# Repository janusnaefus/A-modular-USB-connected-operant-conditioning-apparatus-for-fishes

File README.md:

# A-modular-USB-connected-operant-conditioning-apparatus-for-fishes
Software and hardware blueprints for the corresponding publication in Behavioral Ecology and Sociobiology

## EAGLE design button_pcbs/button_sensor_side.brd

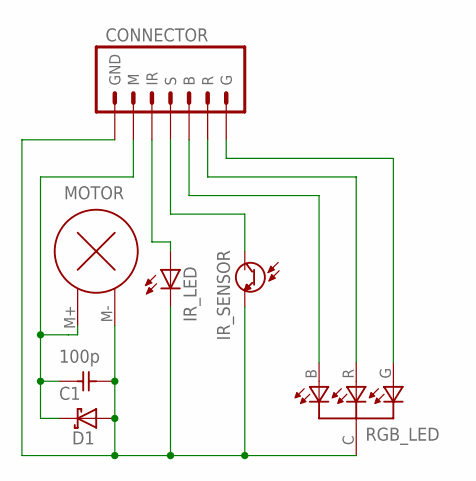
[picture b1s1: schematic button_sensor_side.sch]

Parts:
C1: 100p; C0805
CONNECTOR: CONNECTOR_PADS
D1: DIODE_SCHOTTKY; NSR0530HT1G_SCHOTTKY_DIODE
IR_LED: TCR5000_EMITTER; TCR5000_IR_EMITTER
IR_SENSOR: TCR5000_SENSOR; TCR5000_IR_SENSOR
MOTOR: VIBRATION_MOTOR
RGB_LED: APTF1616SEJ3ZGGVBDC_RBG_LED_SMT; APTF1616SEJ3ZGGVBDC_RGB_LED_SMT

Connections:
GND: C1.2, CONNECTOR.GND, CONNECTOR.GND_ (GND), D1.A, IR_LED.C, IR_SENSOR.E, MOTOR.M- (-), RGB_LED.C
unnamed: C1.1, CONNECTOR.M, D1.C, MOTOR.M+ (+)
unnamed: CONNECTOR.S, IR_SENSOR.C
unnamed: CONNECTOR.IR, IR_LED.A
unnamed: CONNECTOR.B, RGB_LED.B (BLUE)
unnamed: CONNECTOR.R, RGB_LED.R (RED)
unnamed: CONNECTOR.G, RGB_LED.G (GREEN)

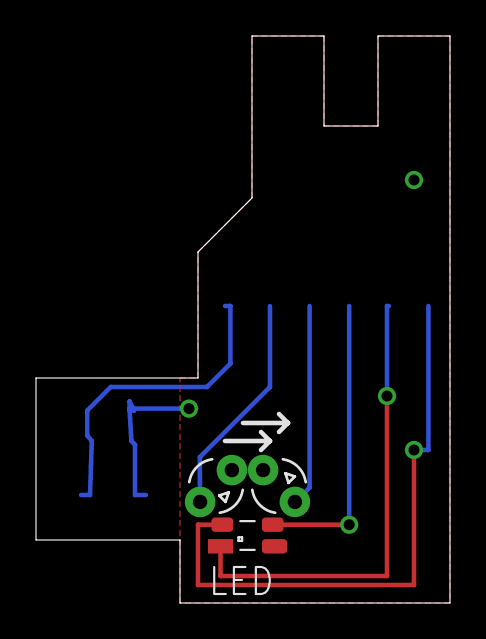
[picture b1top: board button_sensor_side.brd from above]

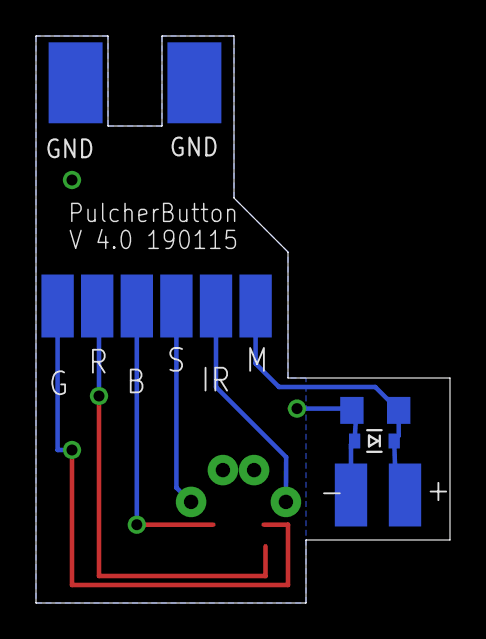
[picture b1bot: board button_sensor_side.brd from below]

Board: 2 copper layers, 23.0 x 31.5 mm, 7 parts (2 on the bottom side), 7 nets.

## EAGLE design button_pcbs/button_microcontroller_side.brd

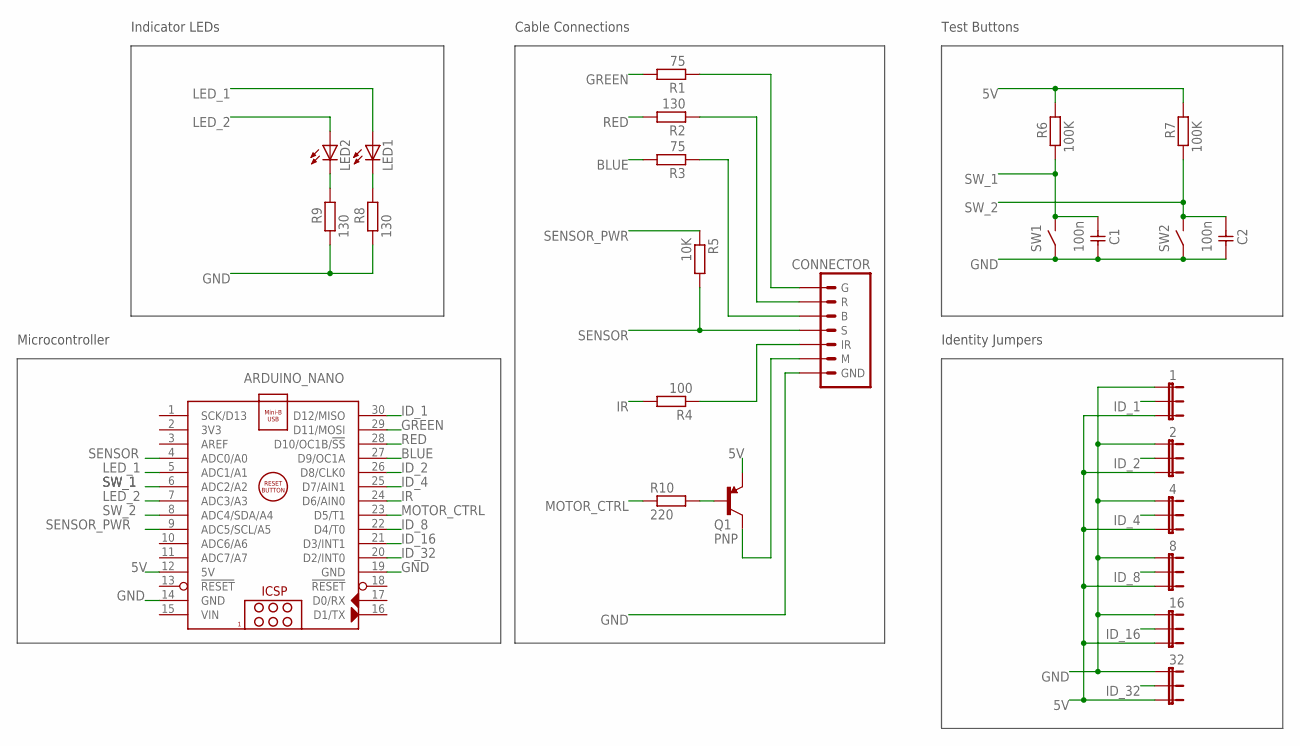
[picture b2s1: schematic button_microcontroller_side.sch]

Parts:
1, 2, 4, 8, 16, 32: JP2E; JP2
ARDUINO_NANO: ARDUINO_NANO
C1, C2: 100n; CAPACITOR
CONNECTOR: CONNECTOR_PADSHOLES; CONNECTOR_ARDUINO_SIDE
LED1, LED2: LED_3MM; TCR5000_IR_EMITTER
Q1: PNP; TO92-
R1, R3: 75; 0204/7
R2, R8, R9: 130; 0204/7
R4: 100; 0204/7
R5: 10K; 0204/7
R6, R7: 100K; 0204/7
R10: 220; 0204/7
SW1, SW2: BUTTON; KS-01Q-01_BUTTON

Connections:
5V: 1.3, 2.3, 4.3, 8.3, 16.3, 32.3, ARDUINO_NANO.12 (5V), Q1.E, R6.2, R7.2
BLUE: ARDUINO_NANO.27 (D9/OC1A), R3.2
GND: 1.1, 2.1, 4.1, 8.1, 16.1, 32.1, ARDUINO_NANO.14 (GND), ARDUINO_NANO.19 (GND), C1.P$1 (1), C2.P$1 (1), CONNECTOR.GND, R8.1, R9.1, SW1.1, SW1.3 (1), SW2.1, SW2.3 (1)
GREEN: ARDUINO_NANO.29 (D11/MOSI), R1.2
ID_1: 1.2, ARDUINO_NANO.30 (D12/MISO)
ID_2: 2.2, ARDUINO_NANO.26 (D8/CLK0)
ID_4: 4.2, ARDUINO_NANO.25 (D7/AIN1)
ID_8: 8.2, ARDUINO_NANO.22 (D4/T0)
ID_16: 16.2, ARDUINO_NANO.21 (D3/INT1)
ID_32: 32.2, ARDUINO_NANO.20 (D2/INT0)
IR: ARDUINO_NANO.24 (D6/AIN0), R4.2
LED_1: ARDUINO_NANO.5 (ADC1/A1), LED1.A
LED_2: ARDUINO_NANO.7 (ADC3/A3), LED2.A
MOTOR: CONNECTOR.M, Q1.C
MOTOR_CTRL: ARDUINO_NANO.23 (D5/T1), R10.1
unnamed: CONNECTOR.IR, R4.1
unnamed: CONNECTOR.B, R3.1
unnamed: CONNECTOR.R, R2.1
unnamed: CONNECTOR.G, R1.1
unnamed: LED1.C, R8.2
unnamed: LED2.C, R9.2
unnamed: Q1.B, R10.2
RED: ARDUINO_NANO.28 (D10/OC1B/!SS), R2.2
SENSOR: ARDUINO_NANO.4 (ADC0/A0), CONNECTOR.S, R5.2
SENSOR_PWR: ARDUINO_NANO.9 (ADC5/SCL/A5), R5.1
SW_1: ARDUINO_NANO.6 (ADC2/A2), C1.P$2 (2), R6.1, SW1.2, SW1.4 (2)
SW_2: ARDUINO_NANO.8 (ADC4/SDA/A4), C2.P$2 (2), R7.1, SW2.2, SW2.4 (2)
VIN: ARDUINO_NANO.15 (VIN)

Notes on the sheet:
Indicator LEDs
Test Buttons
Cable Connections
Identity Jumpers
Microcontroller

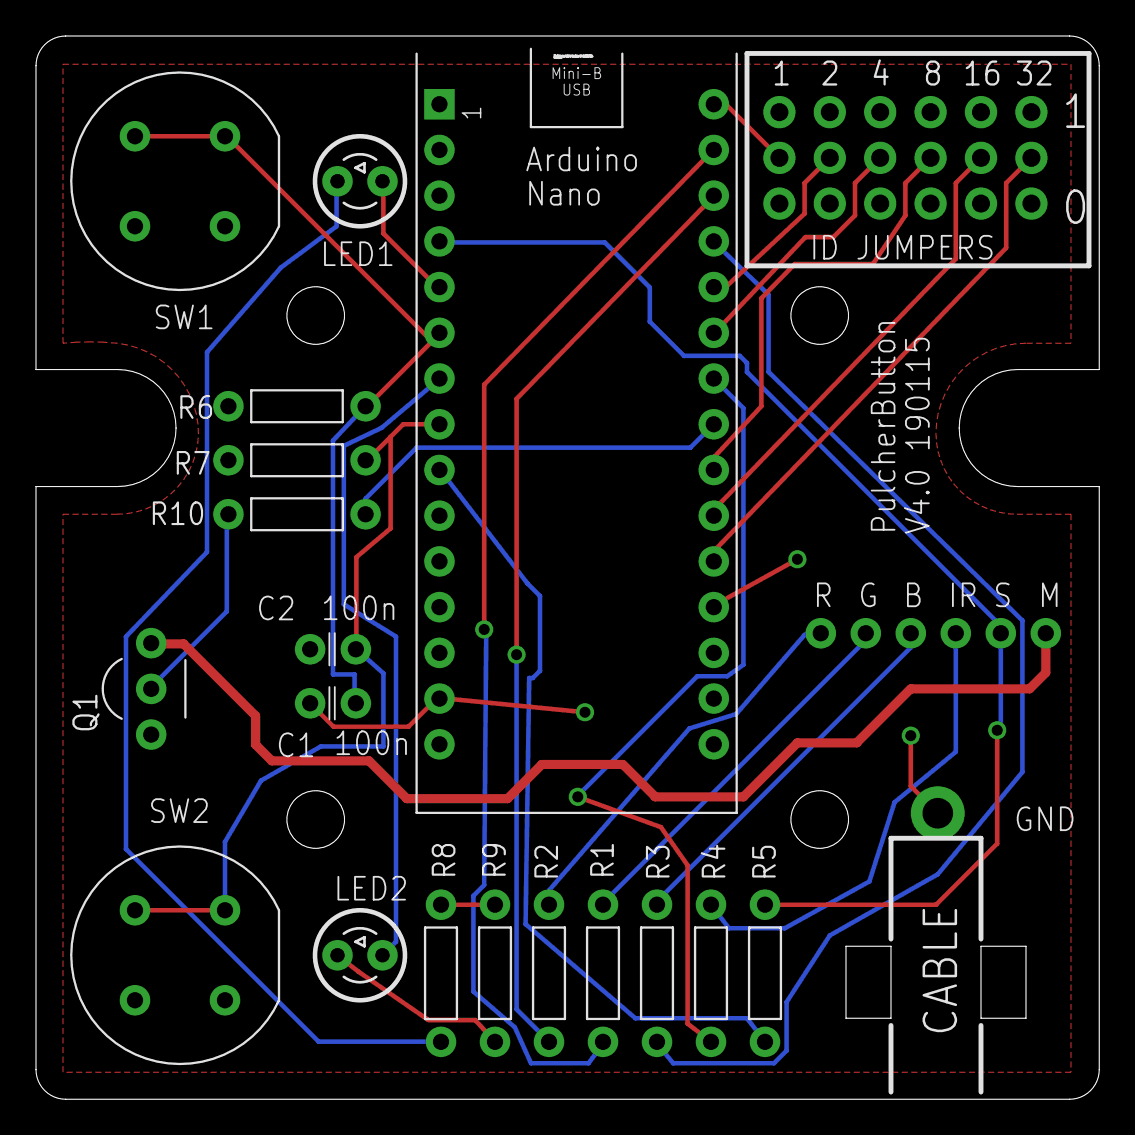
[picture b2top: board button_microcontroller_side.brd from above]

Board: 2 copper layers, 59.1 x 59.1 mm, 25 parts (0 on the bottom side), 27 nets.

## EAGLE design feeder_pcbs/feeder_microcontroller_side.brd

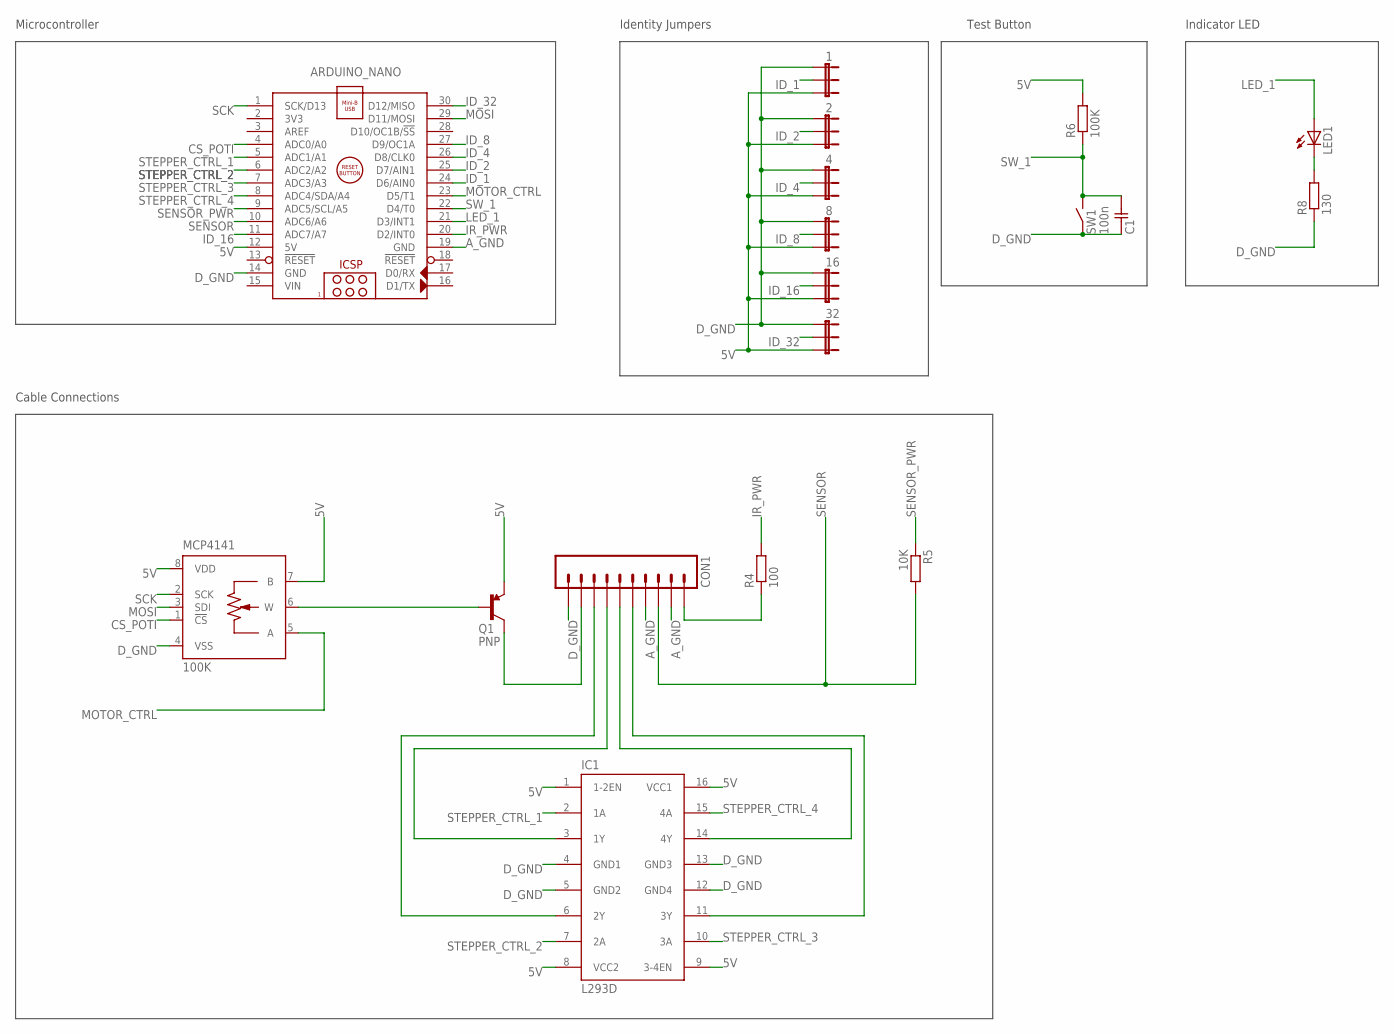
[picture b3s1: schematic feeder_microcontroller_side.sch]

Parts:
1, 2, 4, 8, 16, 32: JP2E; JP2
ARDUINO_NANO: ARDUINO_NANO
C1: 100n; CAPACITOR
CON1: CON_10; CON_10P_1.25_ALIEXPRESS
IC1: L293D; DIL16
LED1: LED_3MM; TCR5000_IR_EMITTER
MCP4141: 100K; DIL08
Q1: PNP; TO92-
R4: 100; 0204/7
R5: 10K; 0204/7
R6: 100K; 0204/7
R8: 130; 0204/7
SW1: BUTTON; KS-01Q-01_BUTTON

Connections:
5V: 1.3, 2.3, 4.3, 8.3, 16.3, 32.3, ARDUINO_NANO.12 (5V), IC1.1 (1-2EN), IC1.8 (VCC2), IC1.9 (3-4EN), IC1.16 (VCC1), MCP4141.7 (B), MCP4141.8 (VDD), Q1.E, R6.2
A_GND: ARDUINO_NANO.19 (GND), CON1.2, CON1.4
CS_POTI: ARDUINO_NANO.4 (ADC0/A0), MCP4141.1 (!CS)
D_GND: 1.1, 2.1, 4.1, 8.1, 16.1, 32.1, ARDUINO_NANO.14 (GND), C1.P$1 (1), CON1.10, IC1.4 (GND1), IC1.5 (GND2), IC1.12 (GND4), IC1.13 (GND3), MCP4141.4 (VSS), R8.1, SW1.1, SW1.3 (1)
ID_1: 1.2, ARDUINO_NANO.24 (D6/AIN0)
ID_2: 2.2, ARDUINO_NANO.25 (D7/AIN1)
ID_4: 4.2, ARDUINO_NANO.26 (D8/CLK0)
ID_8: 8.2, ARDUINO_NANO.27 (D9/OC1A)
ID_16: 16.2, ARDUINO_NANO.11 (ADC7/A7)
ID_32: 32.2, ARDUINO_NANO.30 (D12/MISO)
IR+: CON1.1, R4.1
IR_PWR: ARDUINO_NANO.20 (D2/INT0), R4.2
LED_1: ARDUINO_NANO.21 (D3/INT1), LED1.A
MOSI: ARDUINO_NANO.29 (D11/MOSI), MCP4141.3 (SDI)
MOTOR_CTRL: ARDUINO_NANO.23 (D5/T1), MCP4141.5 (A)
MOTOR_SUPPLY: CON1.9, Q1.C
unnamed: MCP4141.6 (W), Q1.B
unnamed: LED1.C, R8.2
SCK: ARDUINO_NANO.1 (SCK/D13), MCP4141.2 (SCK)
SENSOR: ARDUINO_NANO.10 (ADC6/A6), CON1.3, R5.2
SENSOR_PWR: ARDUINO_NANO.9 (ADC5/SCL/A5), R5.1
STEPPER_CTRL_1: ARDUINO_NANO.5 (ADC1/A1), IC1.2 (1A)
STEPPER_CTRL_2: ARDUINO_NANO.6 (ADC2/A2), IC1.7 (2A)
STEPPER_CTRL_3: ARDUINO_NANO.7 (ADC3/A3), IC1.10 (3A)
STEPPER_CTRL_4: ARDUINO_NANO.8 (ADC4/SDA/A4), IC1.15 (4A)
STEPPER_PWR_1: CON1.7, IC1.3 (1Y)
STEPPER_PWR_2: CON1.8, IC1.6 (2Y)
STEPPER_PWR_3: CON1.5, IC1.11 (3Y)
STEPPER_PWR_4: CON1.6, IC1.14 (4Y)
SW_1: ARDUINO_NANO.22 (D4/T0), C1.P$2 (2), R6.1, SW1.2, SW1.4 (2)
VIN: ARDUINO_NANO.15 (VIN)

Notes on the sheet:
Indicator LED
Test Button
Cable Connections
Identity Jumpers
Microcontroller

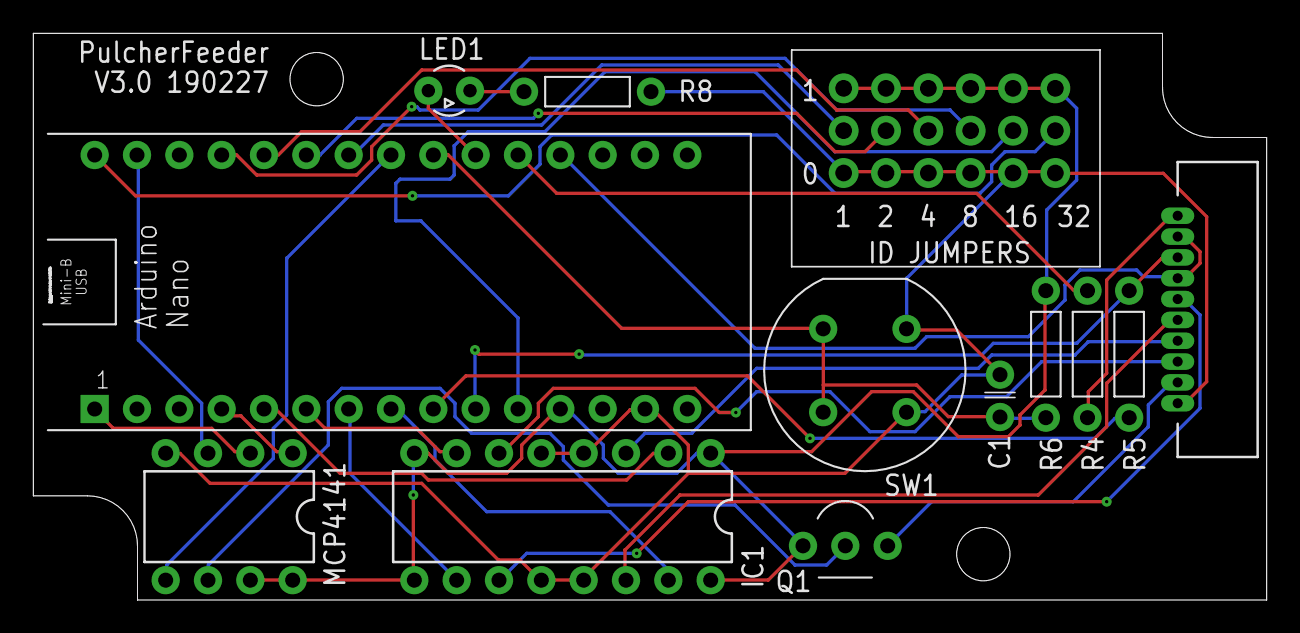
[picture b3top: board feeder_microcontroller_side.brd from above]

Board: 2 copper layers, 74.0 x 34.0 mm, 18 parts (0 on the bottom side), 30 nets.

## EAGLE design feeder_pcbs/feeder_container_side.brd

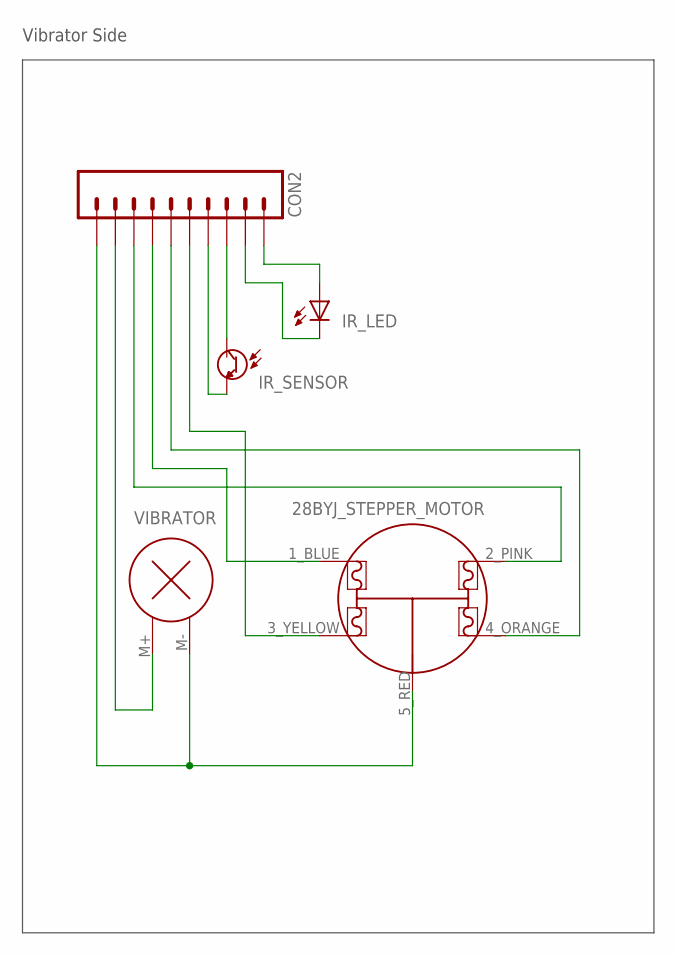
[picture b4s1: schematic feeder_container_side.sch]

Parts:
28BYJ_STEPPER_MOTOR: 28BYJ
CON2: CON_10; CON_10P_1.25_ALIEXPRESS
IR_LED: TCR5000_EMITTER; TCR5000_IR_EMITTER
IR_SENSOR: TCR5000_SENSOR; TCR5000_IR_SENSOR
VIBRATOR: VIBRATION_MOTORVIBRATION_MOTOR_LARGE; VIBRATION_MOTOR_LARGE

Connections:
GND: 28BYJ_STEPPER_MOTOR.5_RED (5_COM), CON2.10, VIBRATOR.M- (-)
IR+: CON2.1, IR_LED.A
IR-: CON2.2, IR_LED.C
MOTOR+: CON2.9, VIBRATOR.M+ (+)
SENSOR+: CON2.3, IR_SENSOR.C
SENSOR-: CON2.4, IR_SENSOR.E
STEPPER_1: 28BYJ_STEPPER_MOTOR.1_BLUE (1), CON2.7
STEPPER_2: 28BYJ_STEPPER_MOTOR.2_PINK (2), CON2.8
STEPPER_3: 28BYJ_STEPPER_MOTOR.3_YELLOW (3), CON2.5
STEPPER_4: 28BYJ_STEPPER_MOTOR.4_ORANGE (4), CON2.6

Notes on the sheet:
Vibrator Side

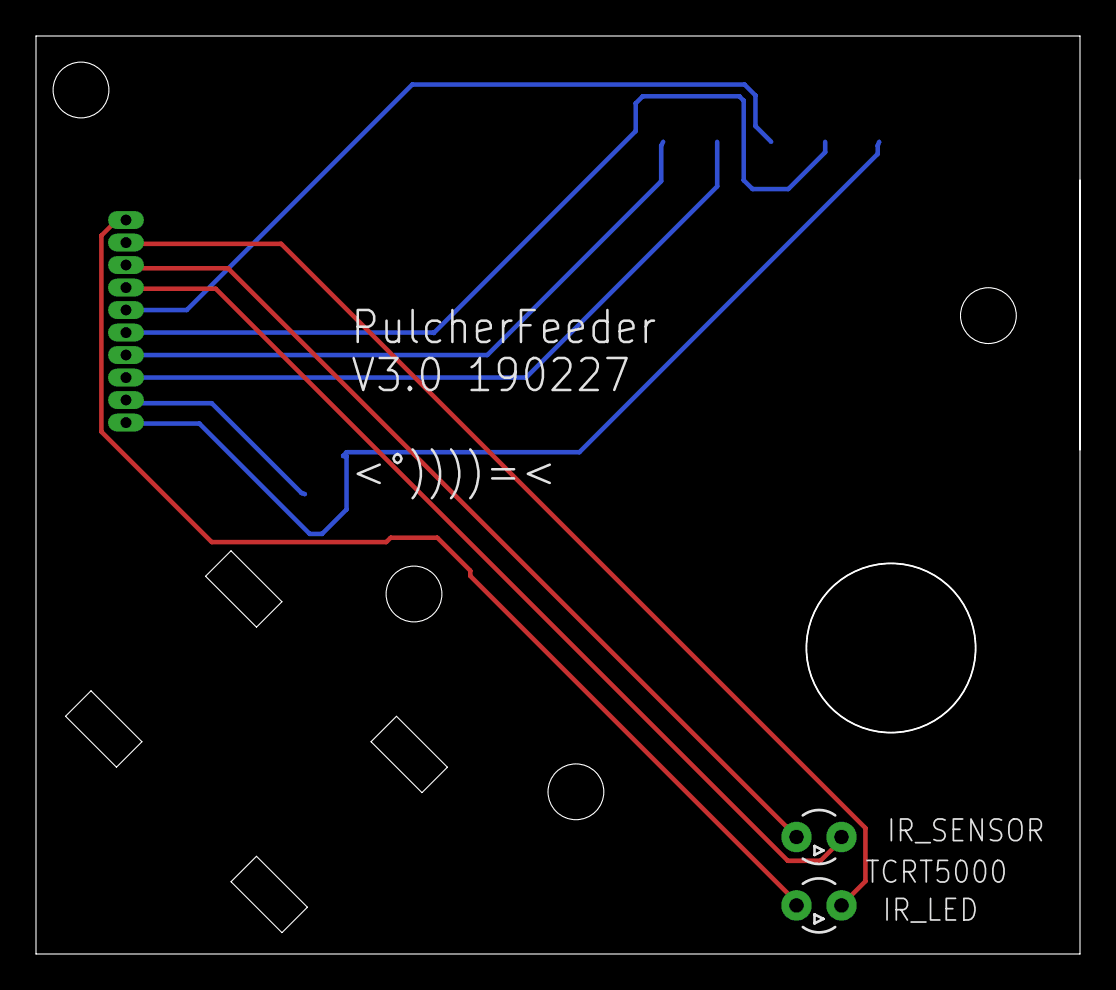
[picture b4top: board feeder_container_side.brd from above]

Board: 2 copper layers, 57.9 x 50.9 mm, 5 parts (1 on the bottom side), 10 nets.

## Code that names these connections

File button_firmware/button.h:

#ifndef BUTTON_H
#define BUTTON_H

#if defined(ARDUINO) && ARDUINO >= 100
#include <Arduino.h>
#else
#include <WProgram.h>
#endif

#define red        10
#define green      11
#define blue        9
#define ir          6
#define motor       5
#define sensor     A0
#define sensor_pwr A5
#define sw1        A2
#define sw2        A4
#define led1       A1
#define led2       A3
#define ID_01      12
#define ID_02       8
#define ID_04       7
#define ID_08       4
#define ID_16       3
#define ID_32       2


#define buf1_size  100
#define buf2_size   10

#define motor_on_pwm 255*2/5


class Button {
public:
  Button(int  _t         = 15,
         long _interval  = 1);

  String readID ();
  void   signal_startup_complete ();
  void   arm (int _red_val   = 0,
              int _green_val = 255,
              int _blue_val  = 0);
  void   disarm();
  bool   triggered();
  void   read_sensor(int _seconds   = 1,
                     int _framerate = 10,
                     int _red_val   = 0,
                     int _green_val = 255,
                     int _blue_val  = 0);
  float  mean_buf1();
  float  mean_buf2();
  bool   sw1_pressed();
  bool   sw2_pressed();
  void   sw1_routine();
  void   sw2_routine();
  void   set_threshold (int _t);
  
  void klick(int kt);
  void klick(int kt, int s);
  void double_sweep(int low, int high, int rate, bool start_low);
  void sweep(int low, int high, int rate, bool start_low);
  void burst(int n, int d1, int d2);
  void klick_1();
  void klick_2();
  void klick_3();
  void klick_4();
  void motor_on();
  void motor_off();
  
private:  
  int  t;
  long interval;
  int  buf1[buf1_size];
  int  buf2[buf2_size];
  int  top1;
  int  top2;
  unsigned long currentMillis;
  unsigned long previousMillis;
  
  bool armed;
};

#endif

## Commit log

2020-05-28 Create temp
